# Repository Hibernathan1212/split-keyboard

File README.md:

# SPlitty

An ergonomic ortholinear split keyboard made to be low profile yet enjoyable and comfortable to use. It features a 6 column by 3 row layout similar to the Corne ergo keyboard but instead with a full width bottom "thumb cluster" that hopefully helps in moving from a traditional keyboard to a split ergo thumb cluster. This is mostly based around many of my current workflows being based around using CMD CTRL and ALT together on my mac so I wanted a way to reliably (no mod tap/hold on home row) press all of them while pressing all the other keys. I have an absolem/voyager style sticking out thumb cluster which allows for a more natural open hand. I wanted to make this project to help with the uncomfortable ergonomics of my desk that make me hunch forward to my keyboard whereas I'd rather my arms be further apart.

## Features

- Ortholinear
- Column staggered
- 48 keys
- Pinky splay
- 128x32 OLED Displays
- Customizable tilt with tent legs
- ZMK Firmware
- Low Profile Choc Linear Switches
- Wireless
- Hotswappable

## CAD

Uses a mix between a floating tray mount (resting on top of pillars) and a floating integrated plate on a lip to get the benefits of rigidity from tray mount without being too rigid and also alignment from plate.

Made in Onshape.

## PCB

Made in Kicad

### Schematic

### PCB

## Firmware

Uses ZMK and is customizable to do whatever you want pretty much. Set up to work with ZMK Studio. By default has 4 layers: the default qwerty layout layer, a numpad & function keys layout, a symbols layer, and a nav layer with mouse movements.

## BOM

| Product                             | Amount | Unit Cost (THB) | Price (THB) | Price (USD) | Link                                                                                                                                                                                              |
| ----------------------------------- | ------ | --------------- | ----------- | ----------- | ------------------------------------------------------------------------------------------------------------------------------------------------------------------------------------------------- |
| Kailh Choc Low Profile Switches V1  | 70     | 791.58          | 791.58      | 24.09       | [https://th.aliexpress.com/item/1005005723938995.html](https://th.aliexpress.com/item/1005005723938995.html)                                                                                      |
| Kailh Choc Low Profile Keycaps 1u   | 5\*10  | 135             | 675         | 20.54       | [https://keebd.com/products/ldsa-low-profile-blank-keycaps?variant=43210374185112](https://keebd.com/products/ldsa-low-profile-blank-keycaps?variant=43210374185112)                              |
| Kailh Choc Low Profile Keycaps 1.5u | 1\*2   | 51              | 51          | 1.55        | [https://keebd.com/products/ldsa-low-profile-blank-keycaps?variant=43210375397528](https://keebd.com/products/ldsa-low-profile-blank-keycaps?variant=43210375397528)                              |
| Choc Hotswap Sockets                | 50     | 177.03          | 177.03      | 5.39        | [https://th.aliexpress.com/item/1005008543325730.html](https://th.aliexpress.com/item/1005008543325730.html)                                                                                      |
| Reset Button                        | 2      | 51              | 102         | 3.1         | [https://keebd.com/products/reset-button-panasonic](https://keebd.com/products/reset-button-panasonic?srsltid=AfmBOoqrNr1D5JySXj1dNxAi4vIIM-d_Cx6PHS7UyMUKO7owCQmBtrpF)                           |
| Power Switch                        | 2      | 26              | 52          | 1.58        | [https://keebd.com/products/switch-mini-7-pin-2-slide-positions](https://keebd.com/products/switch-mini-7-pin-2-slide-positions?srsltid=AfmBOooT0UHBg7pBa6EjpS95Rs0mNn8pMlFmb-gIRtZvkFgxmaAJpZwf) |
| Rubber Feet                         | 4      | 73.6            | 73.6        | 2.24        | [https://th.aliexpress.com/item/1005007438396940.html](https://th.aliexpress.com/item/1005007438396940.html)                                                                                      |
| Tenting Feet                        | 4      | 58.83           | 235.32      | 7.16        | [https://th.aliexpress.com/item/1005011724480659.html](https://th.aliexpress.com/item/1005011724480659.html)                                                                                      |
| 403450 750mAh                       | 2      | 130.24          | 260.48      | 7.93        | [https://th.aliexpress.com/item/1005003630012646.html](https://th.aliexpress.com/item/1005003630012646.html)                                                                                      |
| Battery JST PH Connector            | 2      | 51              | 102         | 3.1         | [https://keebd.com/products/jst-power-connector](https://keebd.com/products/jst-power-connector?srsltid=AfmBOopmdEJXwQjZOcXiPiyuZl3NNfB-quLRRi4P3NJ0IHfXKXBFPR9Q)                                 |
| ProMicro nrf52840 Board             | 2      | 106.15          | 212.3       | 6.46        | [https://th.aliexpress.com/item/1005006271779544.html](https://th.aliexpress.com/item/1005006271779544.html)                                                                                      |
| Diodes                              | 1      | 25.78           | 25.78       | 0.78        | [https://th.aliexpress.com/item/1005008826378208.html](https://th.aliexpress.com/item/1005008826378208.html)                                                                                      |
| Oled Display 0.91inch I2C           | 1      | 155.34          | 155.34      | 4.73        | [https://th.aliexpress.com/item/1005008918700196.html](https://th.aliexpress.com/item/1005008918700196.html)                                                                                      |
| PCB left                            | 1      |                 |             | 10          |                                                                                                                                                                                                   |
| PCB right                           | 1      |                 |             | 10          |                                                                                                                                                                                                   |
|                                     |        |                 |             |             |                                                                                                                                                                                                   |
| aliexpress shipping                 |        |                 | 143.8       | 4.38        |                                                                                                                                                                                                   |
| keebd shipping                      |        |                 | 230         | 7           |                                                                                                                                                                                                   |
| jlcpcb shipping                     |        |                 |             | 0.05        |                                                                                                                                                                                                   |
|                                     |        |                 |             |             |                                                                                                                                                                                                   |
| Total                               |        |                 |             | 120.08      |                                                                                                                                                                                                   |

(If anyone could help source cheaper materials it would be greatly appreciated)

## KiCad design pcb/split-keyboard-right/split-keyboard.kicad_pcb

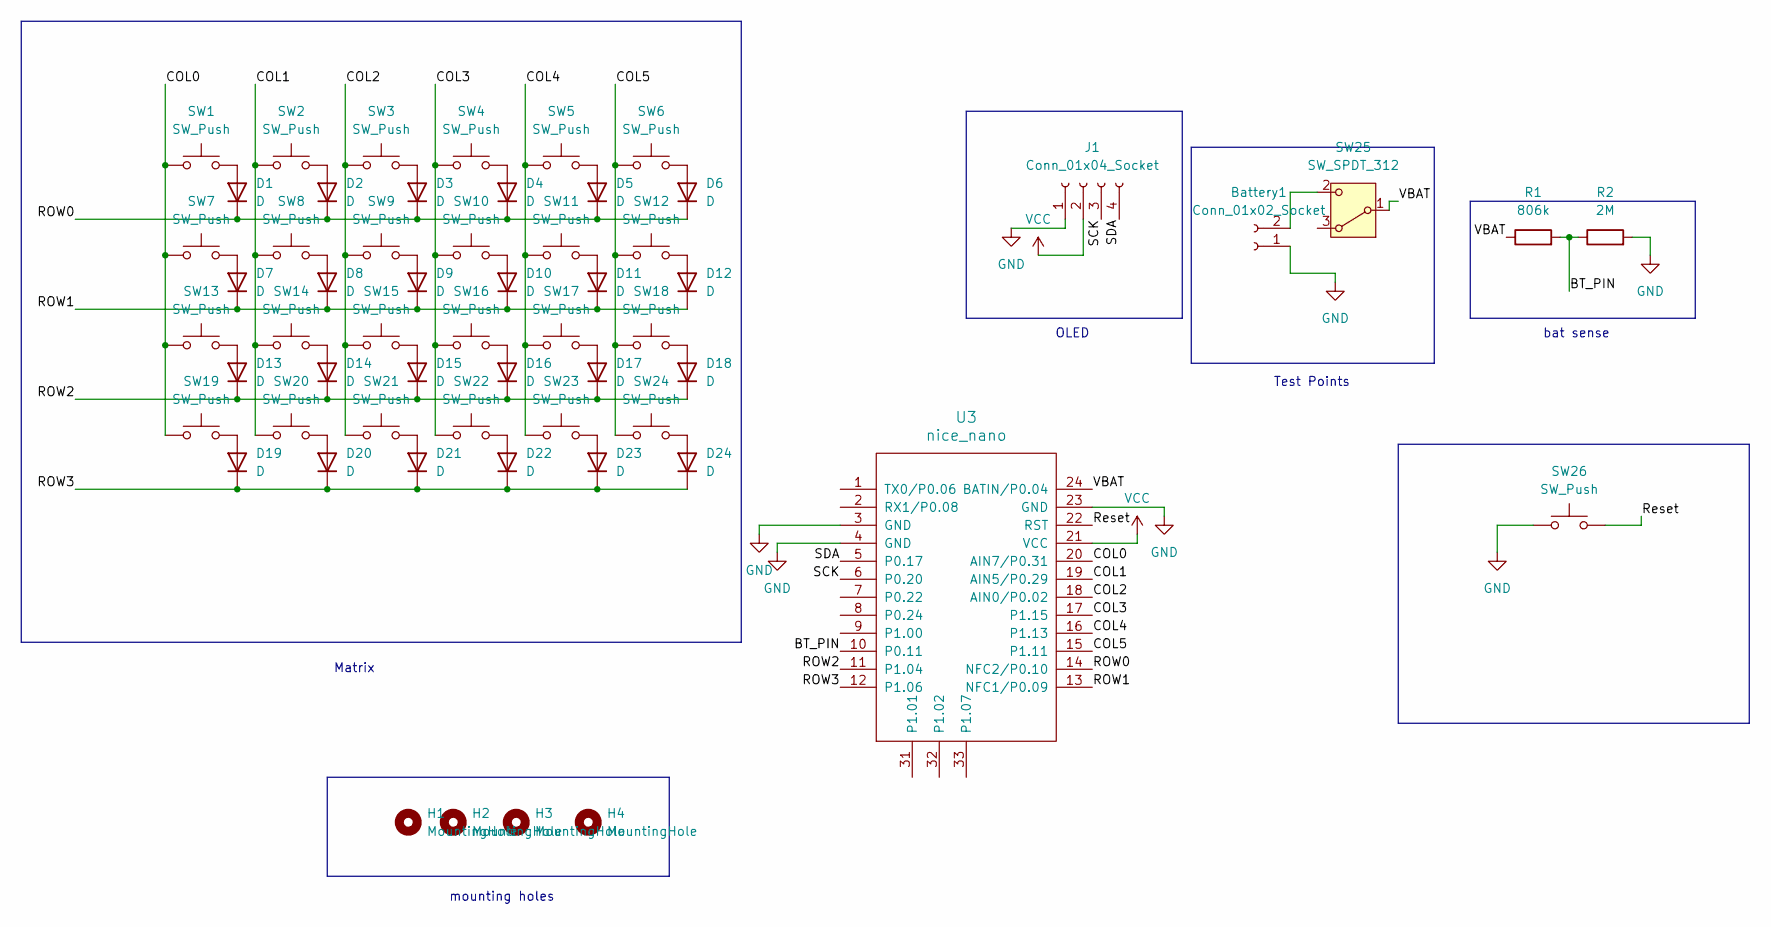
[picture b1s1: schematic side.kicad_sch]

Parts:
Battery1: Conn_01x02_Socket; JST_PH_S2B-PH-K_1x02_P2.00mm_Horizontal
D1, D2, D3, D4, D5, D6, D7, D8, D9, D10, D11, D12, D13, D14, D15, D16, D17, D18, D19, D20, D21, D22, D23, D24: D; D_SOD-123
H1, H2, H3, H4: MountingHole; MountingHole_2.2mm_M2
J1: Conn_01x04_Socket; ER_OLEDM0.91_1x-I2C
R1: 806k; R_0805_2012Metric
R2: 2M; R_0805_2012Metric
SW1, SW2, SW3, SW4, SW5, SW6, SW7, SW8, SW9, SW10, SW11, SW12, SW13, SW14, SW15, SW16, SW17, SW18, SW19, SW20, SW21, SW22, SW23: SW_Push; SW_choc_v1_HS_CPG135001S30_1u
SW24: SW_Push; SW_choc_v1_HS_CPG135001S30_1.5u
SW25: SW_SPDT_312; ALPS_SSSS811101
SW26: SW_Push; Panasonic_EVQPUJ_EVQPUA
U3: nice_nano

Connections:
/left/BT_PIN: R1.2, R2.1, U3.10 (P0.11)
/left/COL0: SW1.1, SW7.1, SW13.1, SW19.1, U3.20 (AIN7/P0.31)
/left/COL1: SW2.1, SW8.1, SW14.1, SW20.1, U3.19 (AIN5/P0.29)
/left/COL2: SW3.1, SW9.1, SW15.1, SW21.1, U3.18 (AIN0/P0.02)
/left/COL3: SW4.1, SW10.1, SW16.1, SW22.1, U3.17 (P1.15)
/left/COL4: SW5.1, SW11.1, SW17.1, SW23.1, U3.16 (P1.13)
/left/COL5: SW6.1, SW12.1, SW18.1, SW24.1, U3.15 (P1.11)
/left/ROW0: D1.1 (K), D2.1 (K), D3.1 (K), D4.1 (K), D5.1 (K), D6.1 (K), U3.14 (NFC2/P0.10)
/left/ROW1: D7.1 (K), D8.1 (K), D9.1 (K), D10.1 (K), D11.1 (K), D12.1 (K), U3.13 (NFC1/P0.09)
/left/ROW2: D13.1 (K), D14.1 (K), D15.1 (K), D16.1 (K), D17.1 (K), D18.1 (K), U3.11 (P1.04)
/left/ROW3: D19.1 (K), D20.1 (K), D21.1 (K), D22.1 (K), D23.1 (K), D24.1 (K), U3.12 (P1.06)
/left/Reset: SW26.2, U3.22 (RST)
/left/SCK: J1.3, U3.6 (P0.20)
/left/SDA: J1.4, U3.5 (P0.17)
/left/VBAT: R1.1, SW25.1 (B), U3.24 (BATIN/P0.04)
GND: Battery1.1, J1.1, R2.2, SW26.1, U3.3 (GND), U3.4 (GND), U3.23 (GND)
unnamed: Battery1.2, SW25.2 (C)
unnamed: D1.2 (A), SW1.2
unnamed: D2.2 (A), SW2.2
unnamed: D3.2 (A), SW3.2
unnamed: D4.2 (A), SW4.2
unnamed: D5.2 (A), SW5.2
unnamed: D6.2 (A), SW6.2
unnamed: D7.2 (A), SW7.2
unnamed: D8.2 (A), SW8.2
unnamed: D9.2 (A), SW9.2
unnamed: D10.2 (A), SW10.2
unnamed: D11.2 (A), SW11.2
unnamed: D12.2 (A), SW12.2
unnamed: D13.2 (A), SW13.2
unnamed: D14.2 (A), SW14.2
unnamed: D15.2 (A), SW15.2
unnamed: D16.2 (A), SW16.2
unnamed: D17.2 (A), SW17.2
unnamed: D18.2 (A), SW18.2
unnamed: D19.2 (A), SW19.2
unnamed: D20.2 (A), SW20.2
unnamed: D21.2 (A), SW21.2
unnamed: D22.2 (A), SW22.2
unnamed: D23.2 (A), SW23.2
unnamed: D24.2 (A), SW24.2
VCC: J1.2, U3.21 (VCC)

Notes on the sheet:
OLED
Matrix
mounting holes
Test Points
bat sense

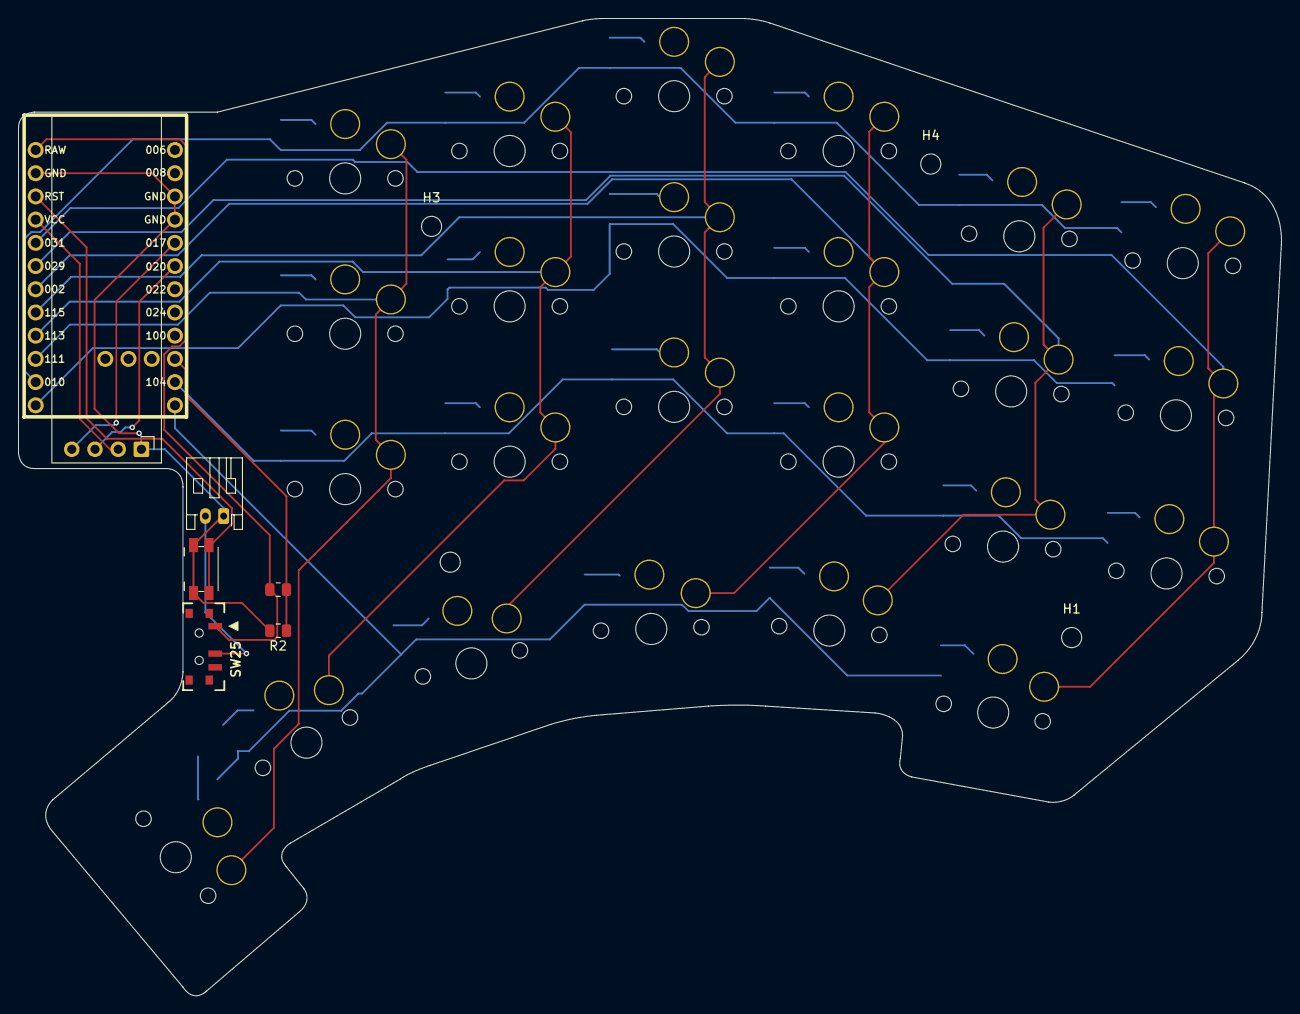
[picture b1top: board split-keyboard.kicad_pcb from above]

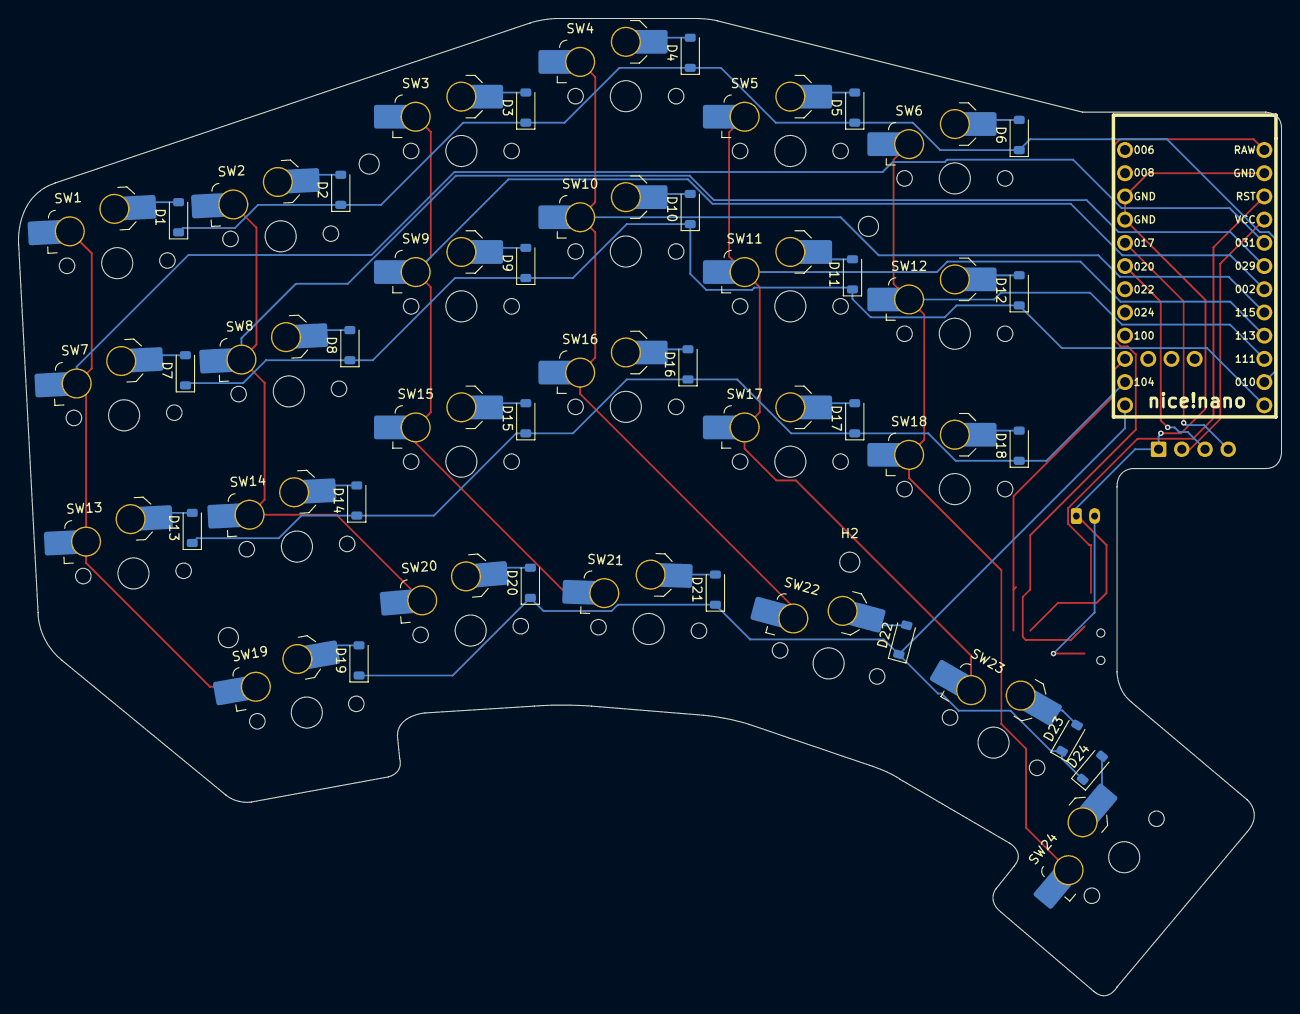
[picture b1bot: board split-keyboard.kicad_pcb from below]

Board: 2 copper layers, 138.2 x 106.9 mm, 59 parts (50 on the bottom side), 42 nets.

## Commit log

2026-03-28 init commit
2026-03-28 remove image
2026-03-28 update image name
2026-03-28 add full image
